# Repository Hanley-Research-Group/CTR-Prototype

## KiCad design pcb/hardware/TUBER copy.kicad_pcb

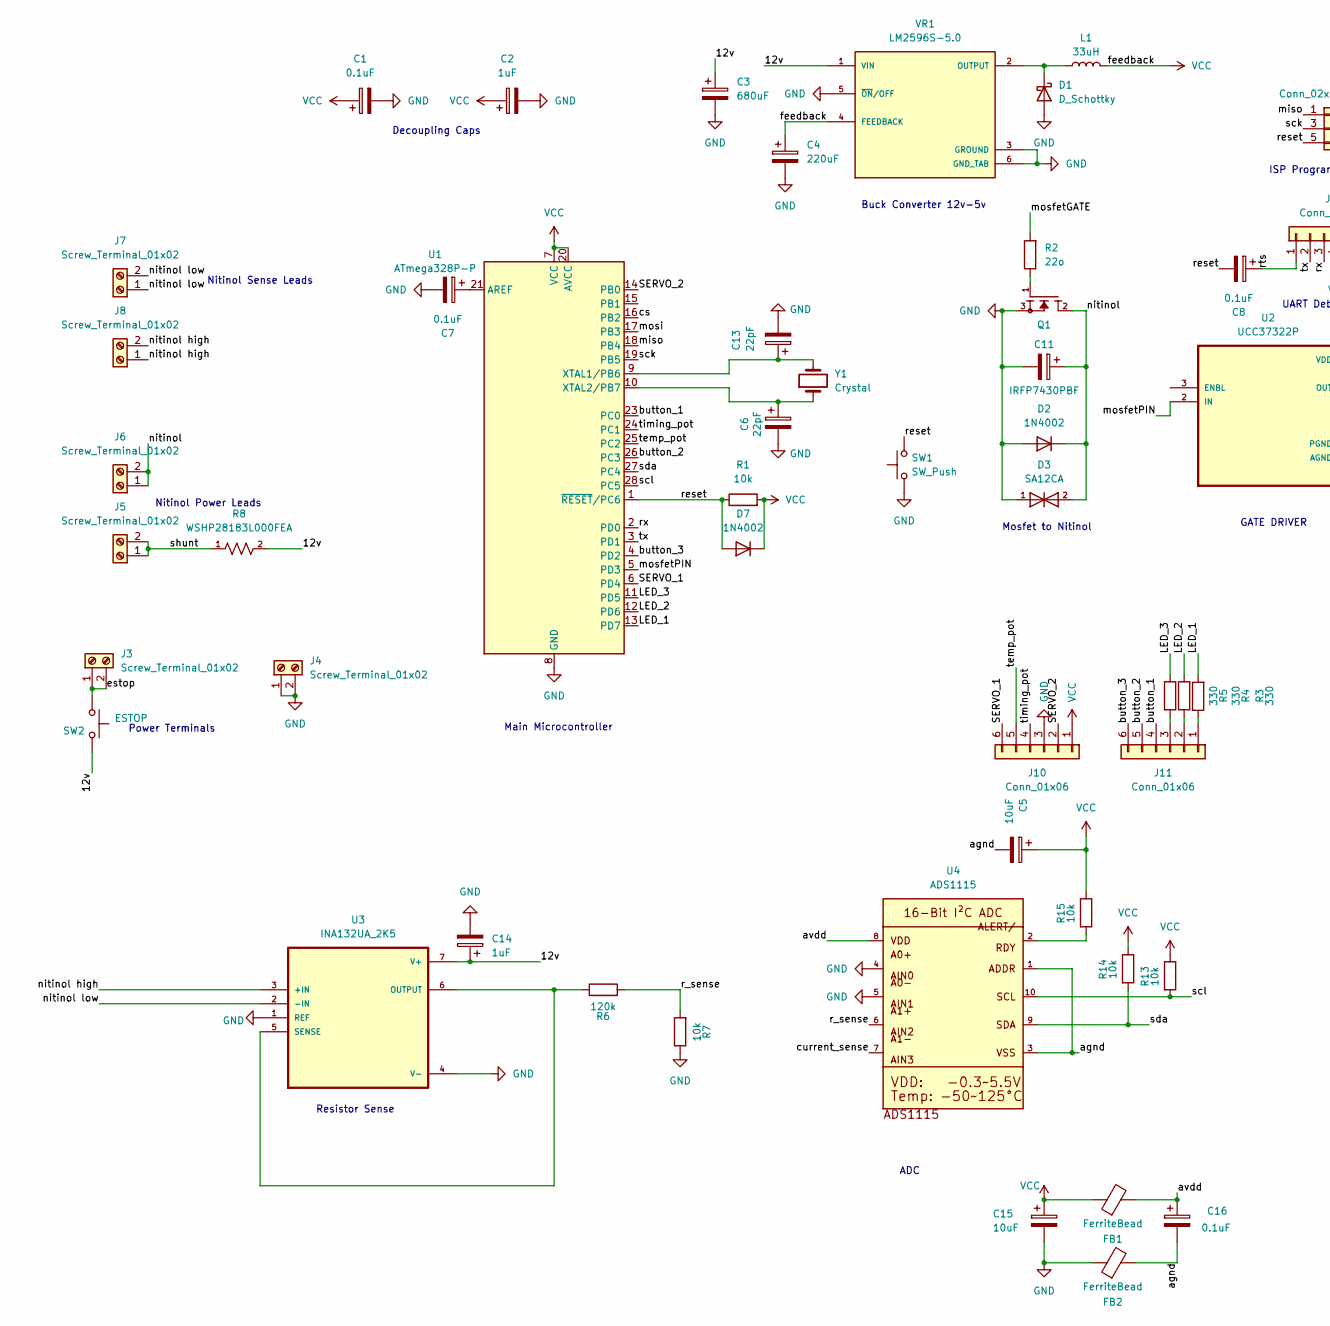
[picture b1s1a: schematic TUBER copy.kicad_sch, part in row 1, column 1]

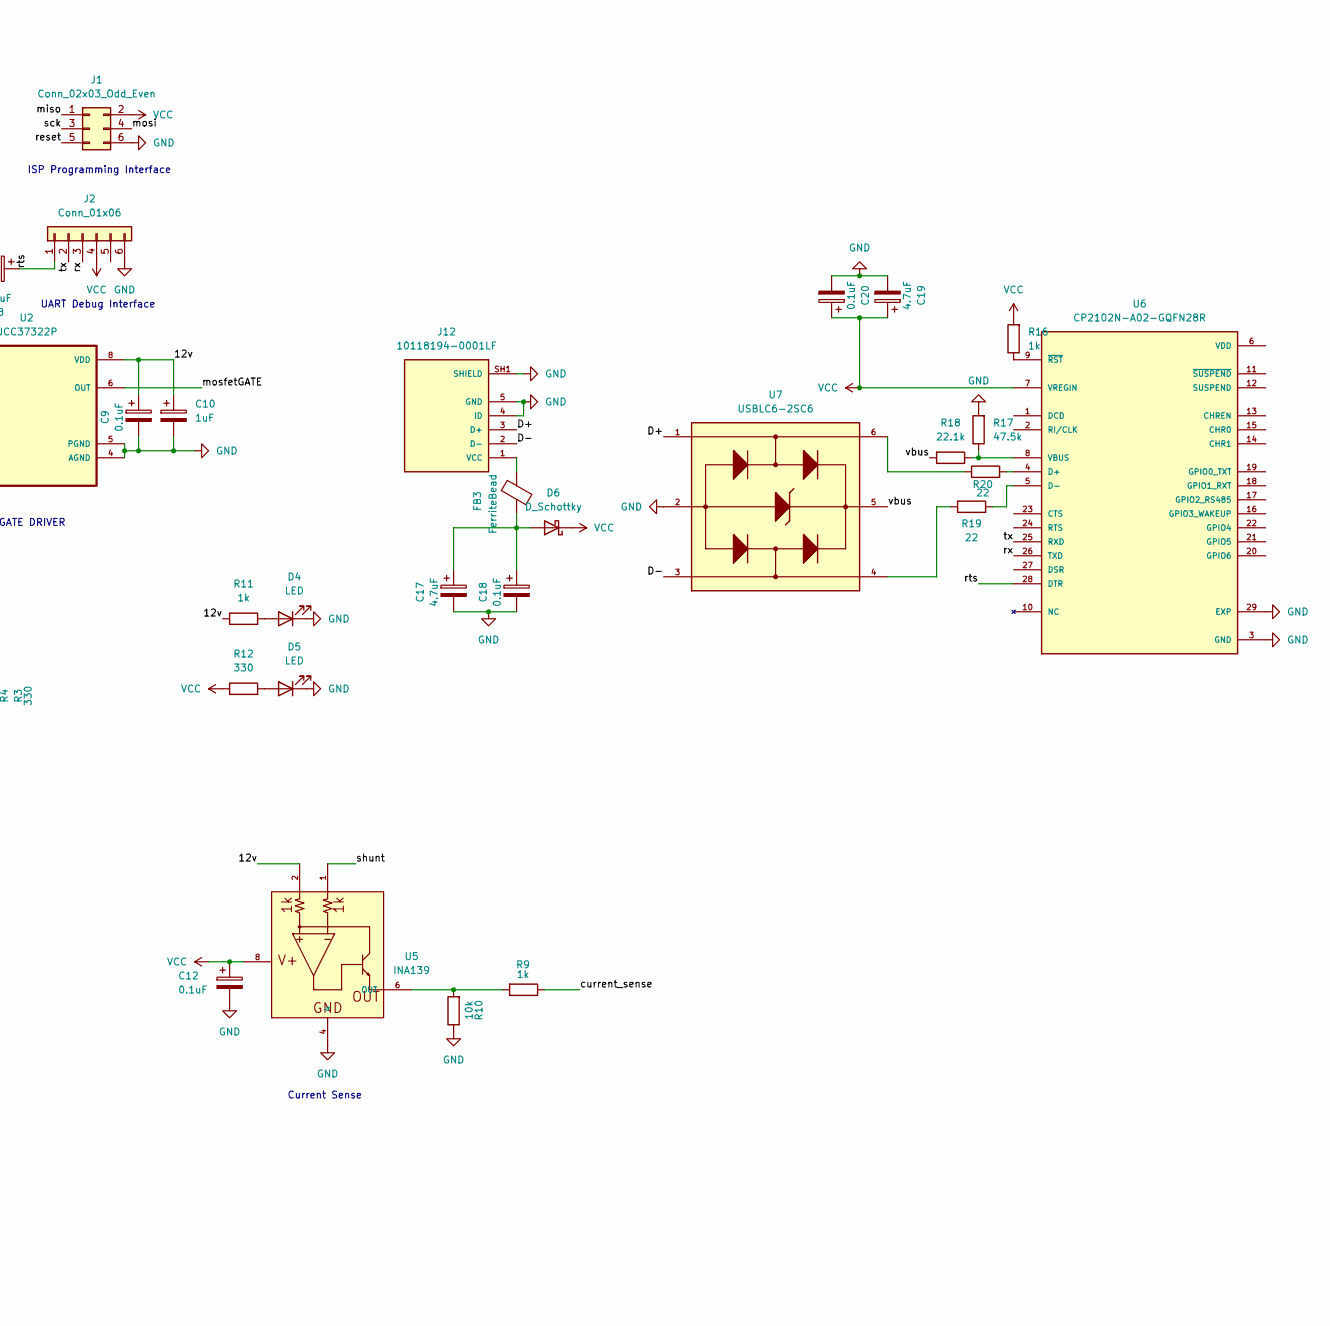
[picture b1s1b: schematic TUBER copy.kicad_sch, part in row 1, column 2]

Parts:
C1, C7, C8, C9, C12, C16, C18, C20: 0.1uF; C_1206_3216Metric_Pad1.33x1.80mm_HandSolder
C2, C10, C14: 1uF; CP_Radial_D5.0mm_P2.50mm
C3: 680uF; CP_Radial_D8.0mm_P3.50mm
C4: 220uF; CP_Radial_D5.0mm_P2.50mm
C5, C15: 10uF; C_1206_3216Metric_Pad1.33x1.80mm_HandSolder
C6, C13: 22pF; C_1206_3216Metric_Pad1.33x1.80mm_HandSolder
C11: 1uF; C_Rect_L7.2mm_W4.5mm_P5.00mm
C17, C19: 4.7uF; CP_Radial_D5.0mm_P2.50mm
D1, D6: D_Schottky; DIOAD2120W130L950D530P
D2, D7: 1N4002; D_DO-41_SOD81_P10.16mm_Horizontal
D3: SA12CA; DO-15B-10
D4, D5: LED; LED_1206_3216Metric_Pad1.42x1.75mm_HandSolder
FB1, FB2, FB3: FerriteBead; BEADC1608X95N
J1: Conn_02x03_Odd_Even; PinHeader_2x03_P2.54mm_Vertical
J2: Conn_01x06; PinHeader_1x06_P2.54mm_Vertical
J3, J4, J5, J6, J7, J8: Screw_Terminal_01x02; TerminalBlock_Xinya_XY308-2.54-2P_1x02_P2.54mm_Horizontal
J10, J11: Conn_01x06; JST_XH_B6B-XH-AM_1x06_P2.50mm_Vertical
J12: 10118194-0001LF; AMPHENOL_10118194-0001LF; PARTREV D
L1: 33uH; INDM3225X240N
Q1: IRFP7430PBF; TO546P1558X498X2499-3; PARTREV 2/19/2015
R1, R7, R10, R13, R14, R15: 10k; R_1206_3216Metric_Pad1.30x1.75mm_HandSolder
R2: 22o; R_1206_3216Metric_Pad1.30x1.75mm_HandSolder
R3, R4, R5, R12: 330; R_1206_3216Metric_Pad1.30x1.75mm_HandSolder
R6: 120k; R_1206_3216Metric_Pad1.30x1.75mm_HandSolder
R8: WSHP28183L000FEA; RES_WSHP28183L000FEA; PARTREV 01-Jan-2026
R9, R11, R16: 1k; R_1206_3216Metric_Pad1.30x1.75mm_HandSolder
R17: 47.5k; R_1206_3216Metric_Pad1.30x1.75mm_HandSolder
R18: 22.1k; R_1206_3216Metric_Pad1.30x1.75mm_HandSolder
R19, R20: 22; R_1206_3216Metric_Pad1.30x1.75mm_HandSolder
SW1: SW_Push; SW_TH_Tactile_Omron_B3F-100x
SW2: ESTOP; SolderWire-0.25sqmm_1x02_P4.5mm_D0.65mm_OD2mm_Relief2x
U1: ATmega328P-P; DIP-28_W7.62mm
U2: UCC37322P; DIP794W45P254L959H508Q8
U3: INA132UA_2K5; SOIC127P599X175-8N
U4: ADS1115; MSOP10
U5: INA139; SOP65P640X120-8N
U6: CP2102N-A02-GQFN28R; IC_CP2102N-A02-GQFN28R; PARTREV 1.5
U7: USBLC6-2SC6; SOT95P280X145-6N
VR1: LM2596S-5.0; TO170P1524X483-6N; PARTREV E
Y1: Crystal; Crystal_HC49-U_Vertical

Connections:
/D+: J12.3 (D+), U7.1
/D-: J12.2 (D-), U7.3
/LED_1: R5.2, U1.13 (PD7)
/LED_2: R4.2, U1.12 (PD6)
/LED_3: R3.1, U1.11 (PD5)
/SERVO_1: J10.6, U1.6 (PD4)
/SERVO_2: J10.2, U1.14 (PB0)
/agnd: C5.2, C16.2, FB2.2, U4.1, U4.3
/avdd: C16.1, FB1.2, U4.8
/button_1: J11.4, U1.23 (PC0)
/button_2: J11.5, U1.26 (PC3)
/button_3: J11.6, U1.4 (PD2)
/cs: U1.16 (PB2)
/current_sense: R9.1, U4.7
/estop: J3.1, J3.2, SW2.1
/miso: J1.1, U1.18 (PB4)
/mosfetGATE: R2.2, U2.6 (OUT), U2.7 (OUT)
/mosfetPIN: U1.5 (PD3), U2.2 (IN)
/mosi: J1.4, U1.17 (PB3)
/nitinol: C11.1, D2.1 (K), D3.2, J6.1, J6.2, Q1.2
/nitinol high: J8.1, J8.2, U3.3 (+IN)
/nitinol low: J7.1, J7.2, U3.2 (-IN)
/r_sense: R6.2, R7.2, U4.6
/reset: C8.2, D7.2 (A), J1.5, R1.1, SW1.2, U1.1 (~RESET/PC6)
/rts: C8.1, J2.1, U6.28 (DTR)
/rx: J2.3, U1.2 (PD0), U6.26 (TXD)
/sck: J1.3, U1.19 (PB5)
/scl: R13.2, U1.28 (PC5), U4.10
/sda: R14.2, U1.27 (PC4), U4.9
/shunt: J5.1, J5.2, R8.1, U5.1
/temp_pot: J10.5, U1.25 (PC2)
/timing_pot: J10.4, U1.24 (PC1)
/tx: J2.2, U1.3 (PD1), U6.25 (RXD)
/vbus: R18.2, U7.5
GND: C1.2, C2.2, C3.2, C4.2, C6.2, C7.2, C9.2, C10.2, C11.2, C12.2, C13.2, C14.2, C15.2, C17.2, C18.2, C19.2, C20.2, D1.2 (A), D2.2 (A), D3.1, D4.1 (K), D5.1 (K), FB2.1, J1.6, J2.6, J4.1, J4.2, J10.3, J12.4 (ID), J12.5 (GND), J12.SH1 (SHIELD), J12.SH2 (SHIELD), J12.SH3 (SHIELD), J12.SH4 (SHIELD), J12.SH5 (SHIELD), J12.SH6 (SHIELD), Q1.3, R7.1, R10.1, R17.2, SW1.1, U1.8 (GND), U1.22 (GND), U2.4 (AGND), U2.5 (PGND), U3.1 (REF), U3.4 (V-), U4.4, U4.5, U5.4, U6.3 (GND), U6.29 (EXP), U7.2, VR1.3 (GROUND), VR1.5 (~ON/OFF), VR1.6 (GND_TAB)
unnamed: D1.1 (K), L1.1, VR1.2 (OUTPUT)
unnamed: D4.2 (A), R11.2
unnamed: D5.2 (A), R12.2
unnamed: C17.1, C18.1, D6.2 (A), FB3.2
unnamed: J11.1, R5.1
unnamed: J11.2, R4.1
unnamed: J11.3, R3.2
unnamed: FB3.1, J12.1 (VCC)
unnamed: Q1.1, R2.1
unnamed: R15.2, U4.2
unnamed: R19.1, U7.4
unnamed: R20.1, U7.6
unnamed: C7.1, U1.21 (AREF)
unnamed: C13.1, U1.9 (XTAL1/PB6), Y1.2
unnamed: C6.1, U1.10 (XTAL2/PB7), Y1.1
unnamed: R6.1, U3.5 (SENSE), U3.6 (OUTPUT)
unnamed: R9.2, R10.2, U5.6 (OUT)
unnamed: R20.2, U6.4 (D+)
unnamed: R19.2, U6.5 (D-)
unnamed: R17.1, R18.1, U6.8 (VBUS)
unnamed: R16.1, U6.9 (~RST)
VCC: C1.1, C2.1, C4.1, C5.1, C12.1, C15.1, C19.1, C20.1, D6.1 (K), D7.1 (K), FB1.1, J1.2, J2.4, J10.1, L1.2, R1.2, R12.1, R13.1, R14.1, R15.1, R16.2, U1.7 (VCC), U1.20 (AVCC), U5.8, U6.7 (VREGIN), VR1.4 (FEEDBACK)
VDD: C3.1, C9.1, C10.1, C14.1, R8.2, R11.1, SW2.2, U2.1 (VDD), U2.8 (VDD), U3.7 (V+), U5.2, VR1.1 (VIN)

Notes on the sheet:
Nitinol Sense Leads
GATE DRIVER
Decoupling Caps
Power Terminals
ISP Programming Interface
Current Sense
UART Debug Interface
ADC
Buck Converter 12v-5v
Nitinol Power Leads
Mosfet to Nitinol
Resistor Sense
Main Microcontroller

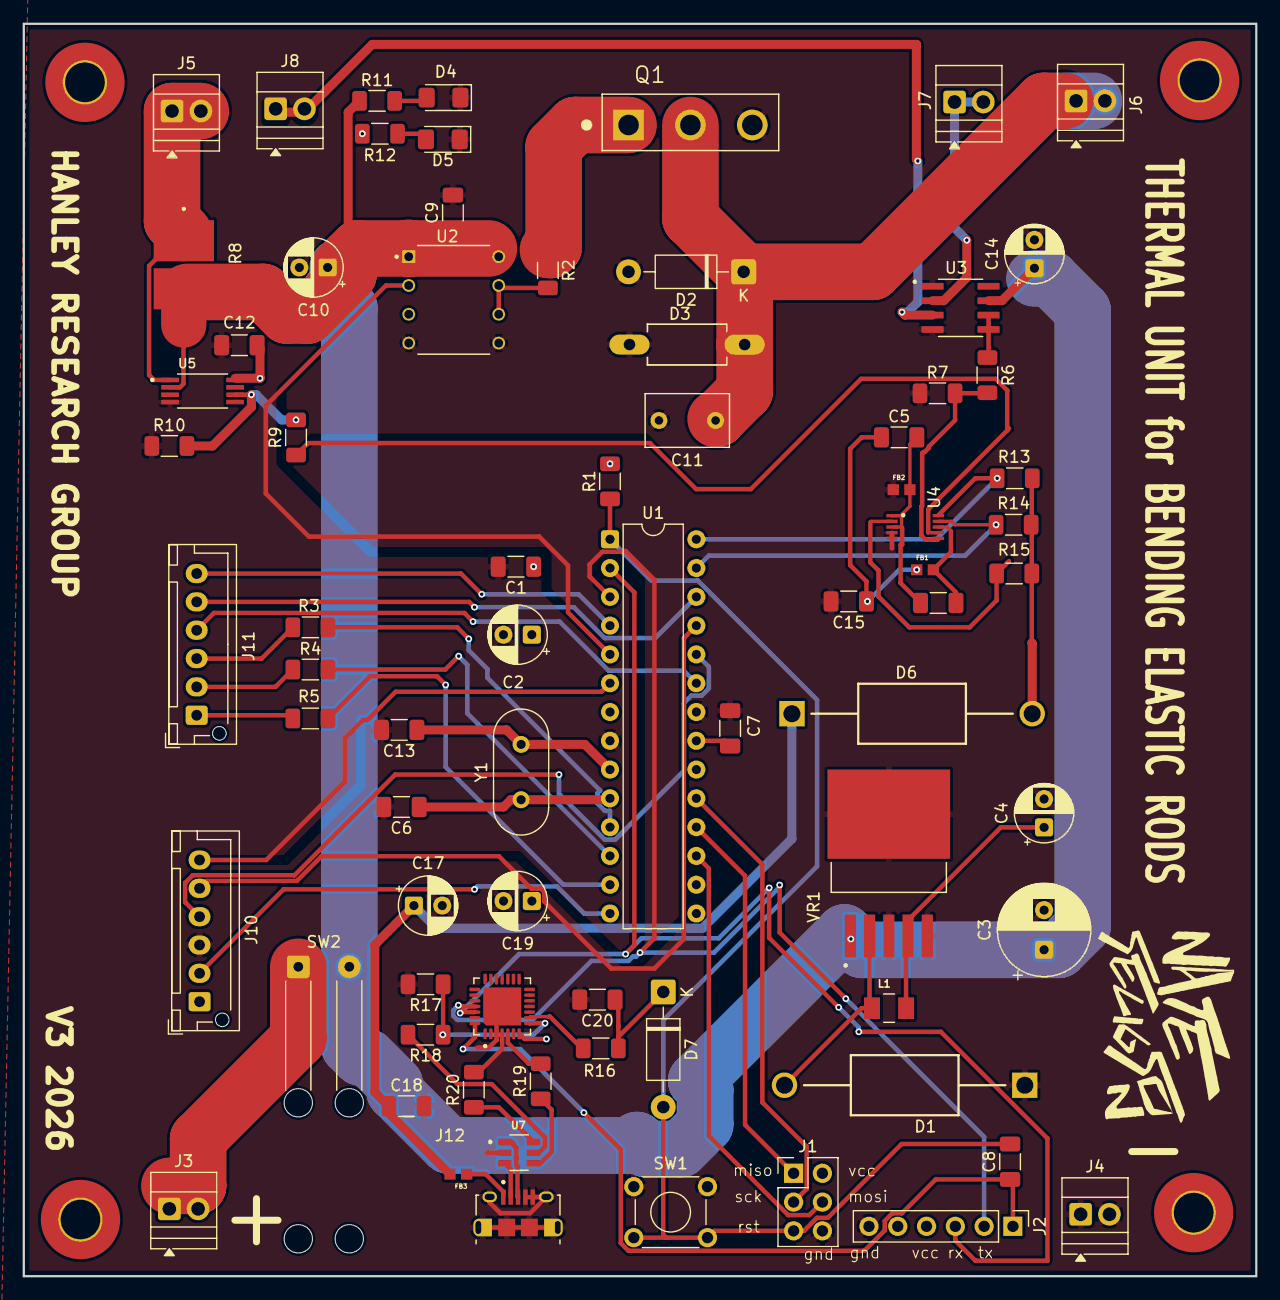
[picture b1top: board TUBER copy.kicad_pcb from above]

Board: 2 copper layers, 108.7 x 110.5 mm, 74 parts (0 on the bottom side), 57 nets.
